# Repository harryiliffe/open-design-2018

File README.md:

# open-design-2018
A repository for the open design course. A place for us to document everything we do and achieve. Yay team Zesty

Check out the blog:
https://harryiliffe.github.io/open-design-2018/

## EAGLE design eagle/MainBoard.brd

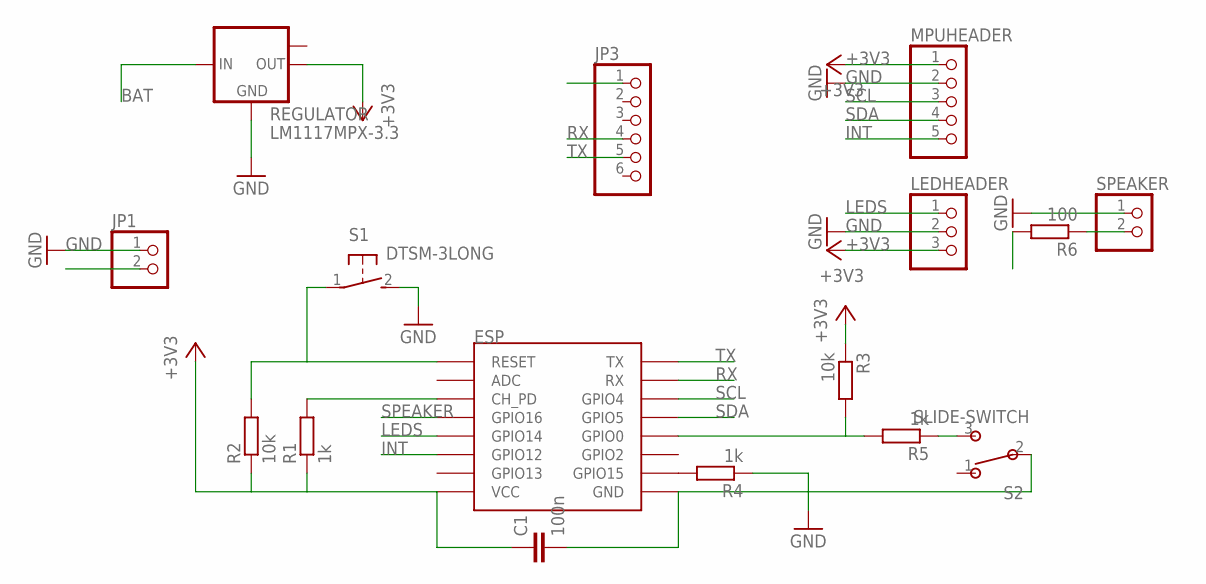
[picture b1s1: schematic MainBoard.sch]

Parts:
C1: 100n; C1206
ESP: ESP12SMD; ESP12-SMD
JP1: PINHD-1X2; 1X02
JP3: PINHD-1X6; 1X06
LEDHEADER: PINHD-1X3; 1X03
MPUHEADER: PINHD-1X5; 1X05
R1, R4, R5: 1k; R1206
R2, R3: 10k; R1206
R6: 100; R1206
REGULATOR: LM1117MPX-3.3; SOT223
S1: DTSM-3LONG
S2: SLIDE-SWITCH; AYZ0102AGRLC
SPEAKER: PINHD-1X2; 1X02

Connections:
+3V3: C1.1, ESP.VCC, LEDHEADER.3, MPUHEADER.1, R1.1, R2.1, R3.1, REGULATOR.2 (OUT)
BAT: JP1.2, REGULATOR.3 (IN)
GND: C1.2, ESP.GND, JP1.1, JP3.1, LEDHEADER.2, MPUHEADER.2, R4.1, REGULATOR.1 (GND), S1.2, S2.2, SPEAKER.1
INT: ESP.GPIO12, MPUHEADER.5
LEDS: ESP.GPIO14, LEDHEADER.1
unnamed: ESP.GPIO0, R3.2, R5.2
unnamed: ESP.CH_PD, R1.2
unnamed: ESP.RESET, R2.2, S1.1
unnamed: ESP.GPIO15, R4.2
unnamed: R5.1, S2.3
unnamed: R6.1, SPEAKER.2
RX: ESP.RXD0 (RX), JP3.4
SCL: ESP.GPIO4, MPUHEADER.3
SDA: ESP.GPIO5, MPUHEADER.4
SPEAKER: ESP.GPIO16, R6.2
TX: ESP.TXD0 (TX), JP3.5

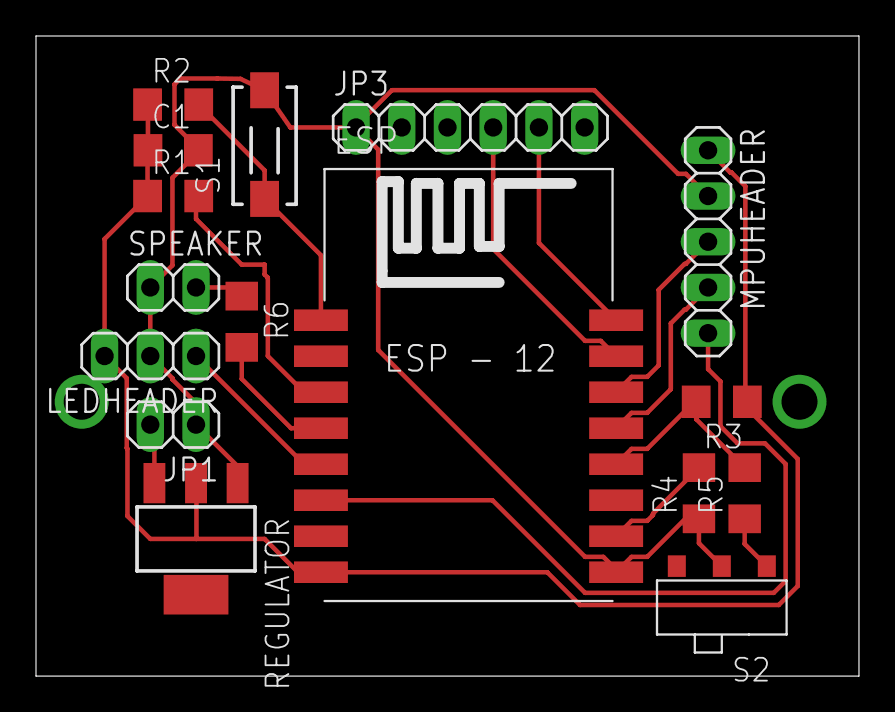
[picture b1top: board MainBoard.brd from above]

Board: 2 copper layers, 45.7 x 35.6 mm, 16 parts (0 on the bottom side), 16 nets.

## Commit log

2018-01-21 Added docs
2018-01-21 updated gitignore
2018-01-22 added blog url
2018-01-22 Added weekly overview pages
2018-01-22 added title
2018-01-22 Made it more inclusive
2018-01-22 removed extra files
2018-01-22 Team Name
2018-01-22 weird words
2018-01-23 Added people that inspire us
2018-01-23 removed wierd words :P
2018-01-23 added catagory research
2018-01-23 fixed imageurl
2018-01-23 formated stuff
2018-01-25 added ideation
2018-01-28 removed used index pages
2018-01-28 added research
2018-01-28 added wearables overview
2018-01-28 removed plugins that dont work
2018-01-28 fixed links
2018-01-28 tidied up
2018-01-28 added page
2018-01-28 added links
2018-01-30 Week 1, Session 2
2018-01-30 Week 1 Presentation
2018-01-30 Adding presentation images
2018-01-30 mindmap images insert
2018-01-30 Week 1 Presentation and Script
2018-01-30 Week 1, Session 2 post
    Upload of mindmap images from week 1
2018-01-30 Updated grammar in page
2018-01-30 Added mindmap images to this post.
2018-01-30 Added image to post
2018-01-30 added presentations tag
2018-01-30 changed name of page url
2018-01-31 Added catagory "presentations"
2018-01-31 hide
2018-01-31 added words
2018-02-09 added code
2018-02-09 added app
2018-02-09 Added speaker test
2018-02-11 added styles
2018-02-11 edited app
2018-02-11 renamed index
2018-02-11 added game1
2018-02-11 edited styles
2018-02-11 added esp post
2018-02-12 Added Pages and links
2018-02-12 Edited companion app
2018-02-12 added ignore for arduino data folder
2018-02-12 added wifi
2018-02-12 moved css to folder
2018-02-12 updated css link
2018-02-12 added titles and ids
2018-02-12 updated modes
2018-02-12 added ota and json parsing
2018-02-12 added js
2018-02-12 removed extra file
2018-02-12 added post
2018-02-12 added button id
2018-02-13 added title and viewport, edited js link
2018-02-13 added file uploader (edit, success)
2018-02-13 removed json
2018-02-13 optimised code
2018-02-13 added sound + game "GregSays"
2018-02-14 Uploaded Script
2018-02-14 saved
2018-02-14 changed formatting
2018-02-14 added captive portal
2018-02-14 added more modes
2018-02-14 moved css and js files
2018-02-14 changed css path
2018-02-14 added config buttons
2018-02-14 added config support
2018-02-14 implemented config
2018-02-14 added emotion sounds
2018-02-14 added example sketch
2018-02-14 renamed posts
2018-02-14 changed colours
2018-02-14 changed colours again
2018-02-14 apped, renamed and updated docs
2018-02-14 fixed coloring
2018-02-14 renamed code folders
2018-02-14 added eagle files
2018-02-14 fixed link
2018-02-15 added pages...hopefully
2018-02-15 Added Liz's images
2018-02-15 edited
2018-02-15 added liz's files
2018-02-15 updated code + also this works so if it breaks come back to this. :)
2018-02-15 Liz Documentation
2018-02-15 added presentation link
2018-02-15 renamed files
2018-02-15 aesthetic blurb written
2018-02-15 Spelt words correctly
2018-02-15 Yay change
2018-02-15 Greg
2018-02-15 cleaned final code
2018-02-15 fixed spelling/naming
2018-02-15 Deleting uneeded images
2018-02-15 added photos
2018-02-15 Liz's pages filled
2018-02-15 Posts
2018-02-15 added images
2018-02-15 made it make more sounds
2018-02-15 Added Final Images
2018-02-15 Added pages
2018-02-15 fixed image links
2018-02-15 fixed liz's shit
2018-02-16 Added how to
2018-02-16 How to
2018-02-16 added videos
